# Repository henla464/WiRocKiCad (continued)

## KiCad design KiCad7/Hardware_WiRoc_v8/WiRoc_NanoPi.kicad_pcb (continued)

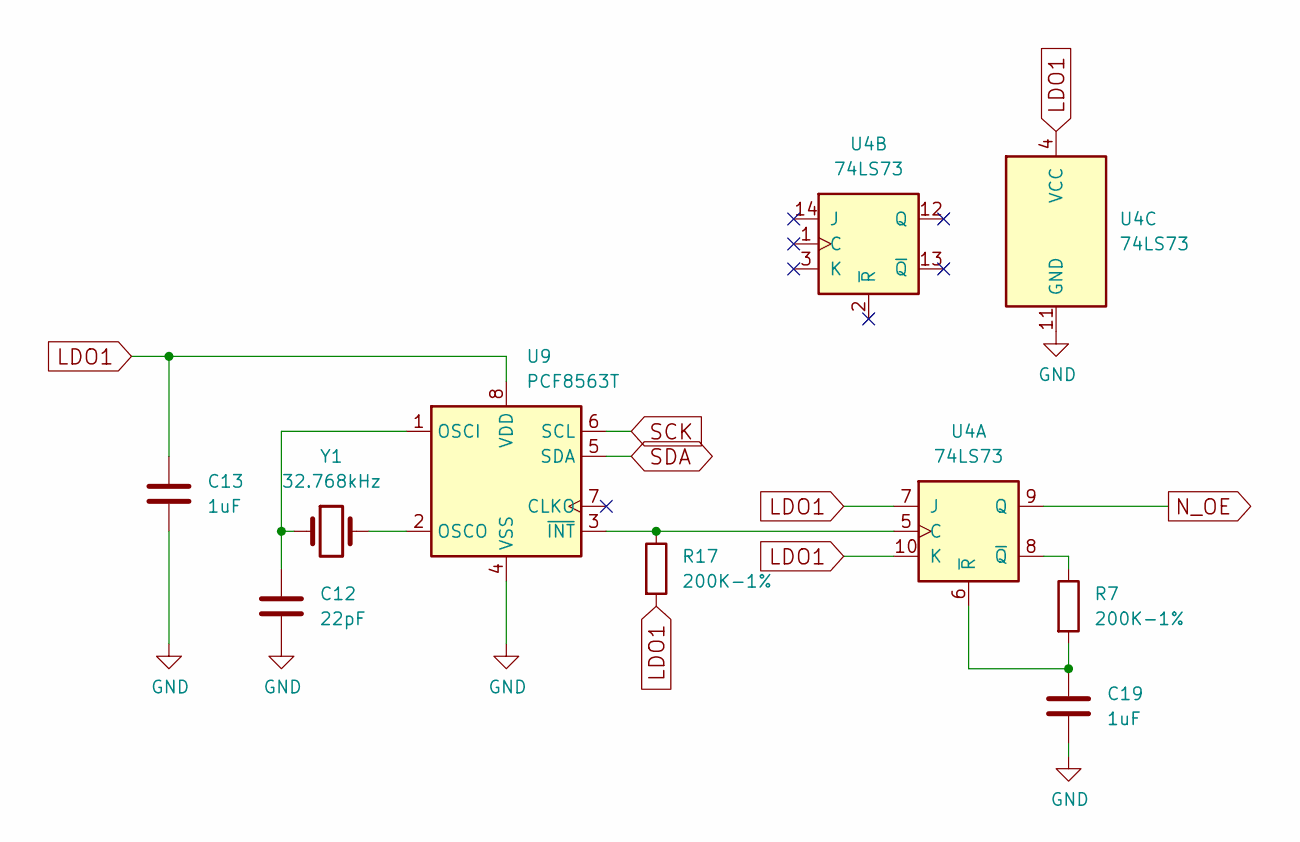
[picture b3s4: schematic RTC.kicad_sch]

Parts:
C12: 22pF; C_0402_1005Metric; ManufacturerPartNumber GRM155R71C223JA01D; LCSC Part # C1555
C13, C19: 1uF; C_0402_1005Metric; ManufacturerPartNumber CL10A105KB8NNNC; LCSC Part # C15849
R7, R17: 200K-1%; R_0402_1005Metric; ManufacturerPartNumber 0603WAF2003T5E; LCSC Part # C25811
U4: 74LS73; SOIC-14_3.9x8.7mm_P1.27mm; ManufacturerPartNumber CD74HC73M96; LCSC Part # C350539
U9: PCF8563T; SOIC-8_3.9x4.9mm_P1.27mm; ManufacturerPartNumber PCF8563T/5,518; LCSC Part # C7440
Y1: 32.768kHz; SMD3215-2P; ManufacturerPartNumber Q13FC1350000400; LCSC Part # C32346

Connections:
GND: C12.2, C13.2, C19.2, U4.11 (GND), U9.4 (VSS); also elsewhere on the board
LDO1: C13.1, R17.2, U4.4 (VCC), U4.7 (J), U4.10 (K), U9.8 (VDD); also elsewhere on the board
N_OE: U4.9 (Q); also elsewhere on the board
unnamed: R17.1, U4.5 (C), U9.3 (~INT)
unnamed: R7.1, U4.8 (~Q)
unnamed: C19.1, R7.2, U4.6 (~R)
unnamed: C12.1, U9.1 (OSCI), Y1.1
unnamed: U9.2 (OSCO), Y1.2
SCK: U9.6 (SCL); also elsewhere on the board
SDA: U9.5 (SDA); also elsewhere on the board

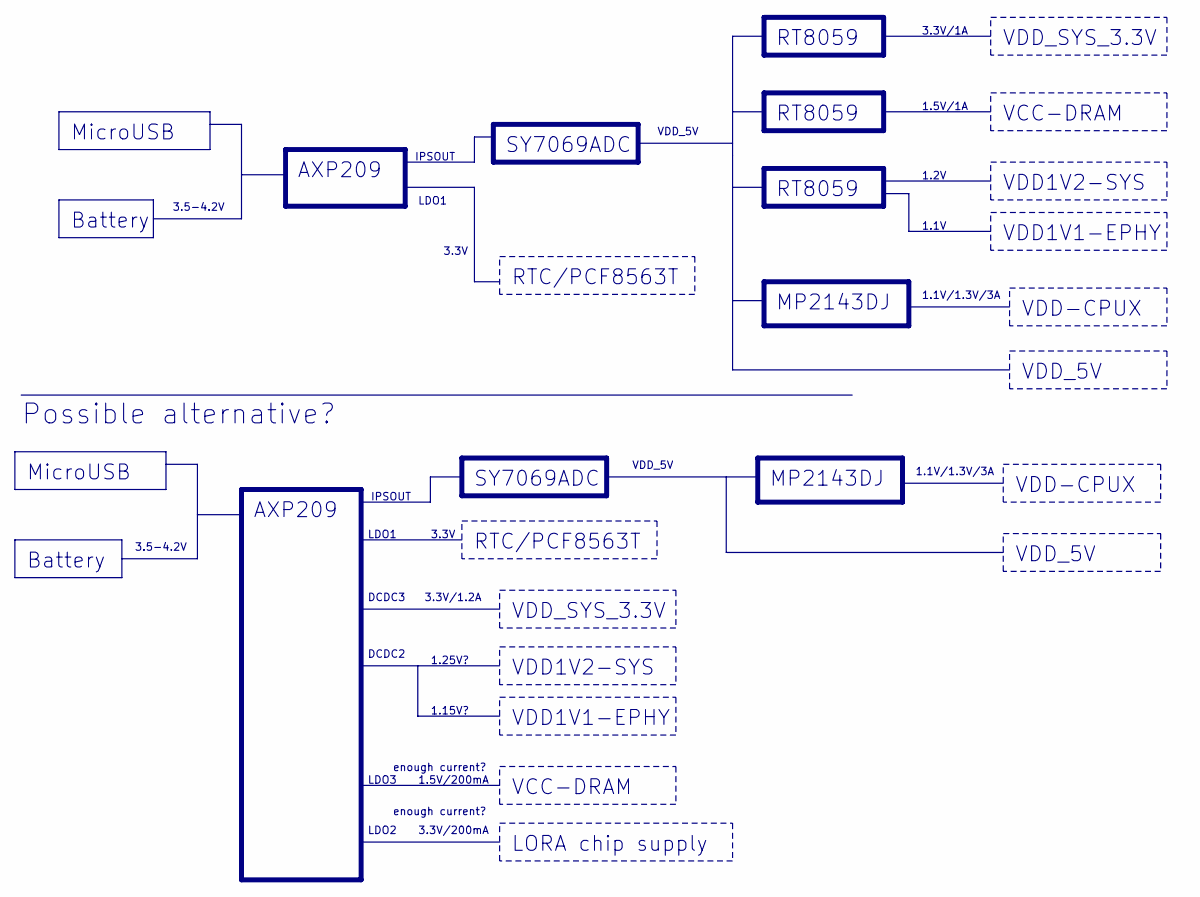
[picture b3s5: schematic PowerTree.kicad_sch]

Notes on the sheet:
VDD1V1-EPHY
VDD-CPUX
MicroUSB
RTC/PCF8563T
SY7069ADC
Battery
VDD1V2-SYS
MP2143DJ
RT8059
VDD_SYS_3.3V
VDD_5V
AXP209
VCC-DRAM
LORA chip supply
1.5V/1A
3.5-4.2V
DCDC3
1.1V/1.3V/3A
Possible alternative?
3.3V/1.2A
1.5V/200mA
1.25V?
IPSOUT
LDO2
3.3V/1A
3.3V/200mA
1.2V
1.15V?
DCDC2
LDO1
LDO3
3.3V
1.1V
enough current?

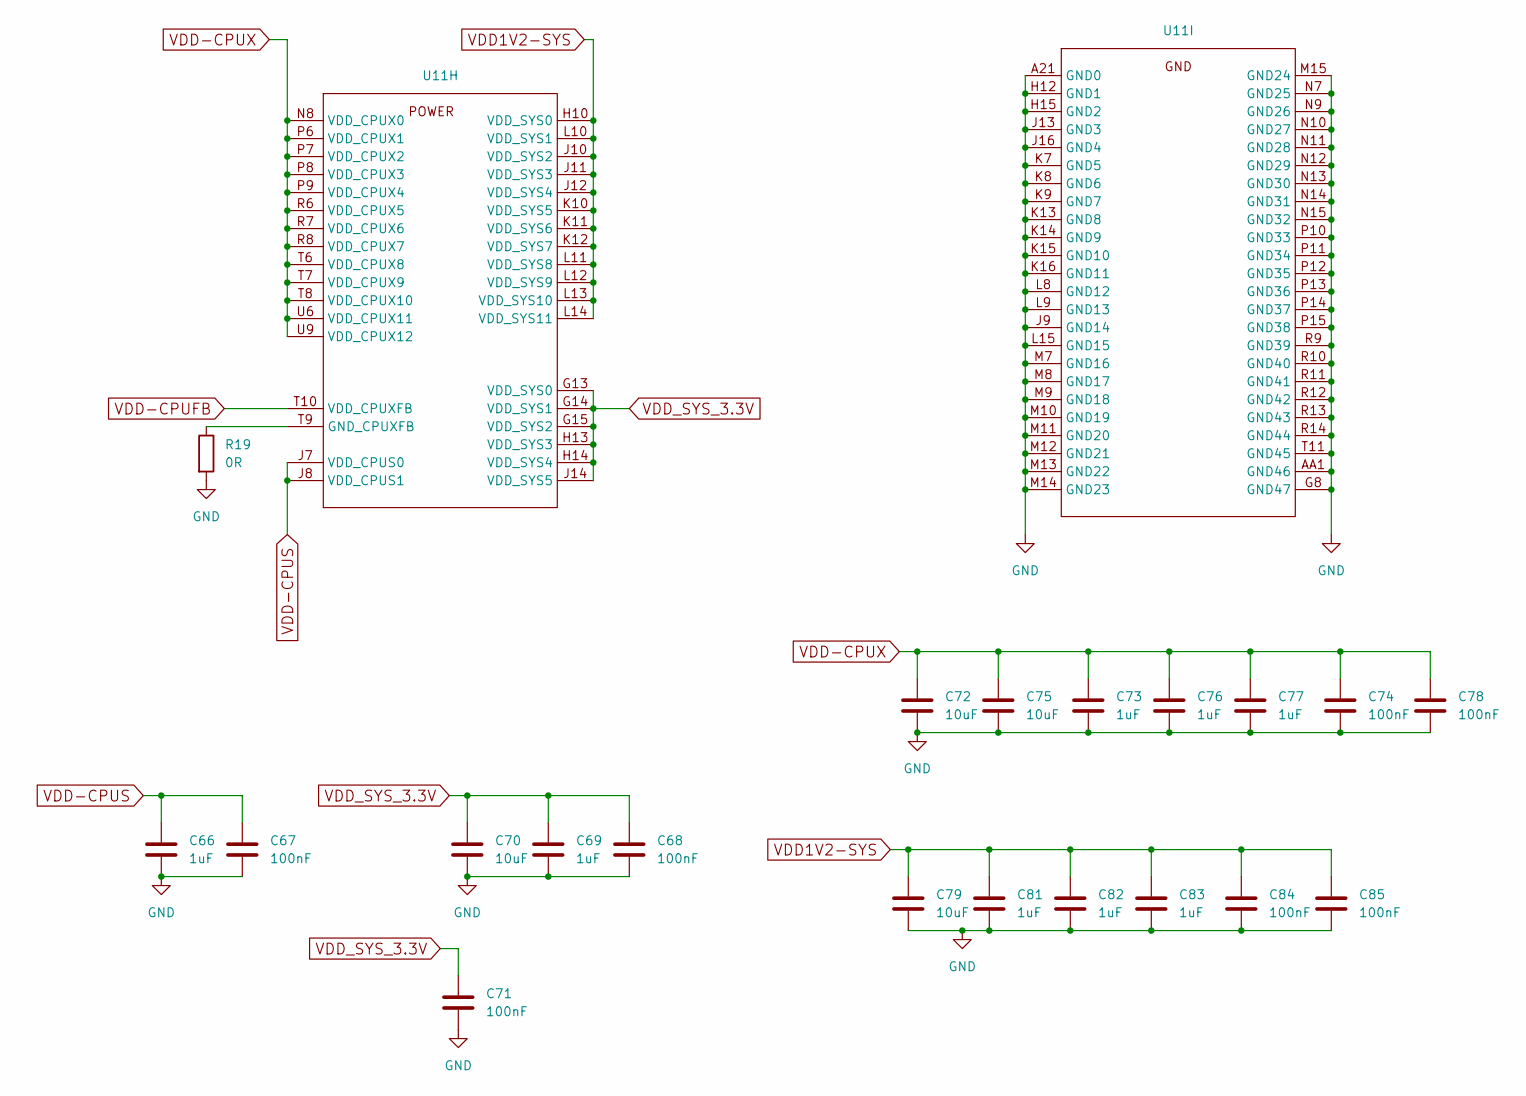
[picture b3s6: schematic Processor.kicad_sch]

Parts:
C66, C69, C73, C76, C77, C81, C82, C83: 1uF; C_0402_1005Metric
C67, C68, C71, C74, C78, C84, C85: 100nF; C_0402_1005Metric
C70, C72, C75, C79: 10uF; C_0402_1005Metric
R19: 0R; R_0402_1005Metric
U11: BGA-347_21x21_14.0x14.0mm

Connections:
GND: C66.2, C67.2, C68.2, C69.2, C70.2, C71.2, C72.2, C73.2, C74.2, C75.2, C76.2, C77.2, C78.2, C79.2, C81.2, C82.2, C83.2, C84.2, C85.2, R19.2, U11.A21 (GND0), U11.AA1 (GND46), U11.G8 (GND47), U11.H12 (GND1), U11.H15 (GND2), U11.J9 (GND14), U11.J13 (GND3), U11.J16 (GND4), U11.K7 (GND5), U11.K8 (GND6), U11.K9 (GND7), U11.K13 (GND8), U11.K14 (GND9), U11.K15 (GND10), U11.K16 (GND11), U11.L8 (GND12), U11.L9 (GND13), U11.L15 (GND15), U11.M7 (GND16), U11.M8 (GND17), U11.M9 (GND18), U11.M10 (GND19), U11.M11 (GND20), U11.M12 (GND21), U11.M13 (GND22), U11.M14 (GND23), U11.M15 (GND24), U11.N7 (GND25), U11.N9 (GND26), U11.N10 (GND27), U11.N11 (GND28), U11.N12 (GND29), U11.N13 (GND30), U11.N14 (GND31), U11.N15 (GND32), U11.P10 (GND33), U11.P11 (GND34), U11.P12 (GND35), U11.P13 (GND36), U11.P14 (GND37), U11.P15 (GND38), U11.R9 (GND39), U11.R10 (GND40), U11.R11 (GND41), U11.R12 (GND42), U11.R13 (GND43), U11.R14 (GND44), U11.T11 (GND45); also elsewhere on the board
unnamed: R19.1, U11.T9 (GND_CPUXFB)
VDD1V2-SYS: C79.1, C81.1, C82.1, C83.1, C84.1, C85.1, U11.H10 (VDD_SYS0), U11.J10 (VDD_SYS2), U11.J11 (VDD_SYS3), U11.J12 (VDD_SYS4), U11.K10 (VDD_SYS5), U11.K11 (VDD_SYS6), U11.K12 (VDD_SYS7), U11.L10 (VDD_SYS1), U11.L11 (VDD_SYS8), U11.L12 (VDD_SYS9), U11.L13 (VDD_SYS10), U11.L14 (VDD_SYS11); also elsewhere on the board
VDD-CPUFB: U11.T10 (VDD_CPUXFB); also elsewhere on the board
VDD-CPUS: C66.1, C67.1, U11.J7 (VDD_CPUS0), U11.J8 (VDD_CPUS1); also elsewhere on the board
VDD-CPUX: C72.1, C73.1, C74.1, C75.1, C76.1, C77.1, C78.1, U11.N8 (VDD_CPUX0), U11.P6 (VDD_CPUX1), U11.P7 (VDD_CPUX2), U11.P8 (VDD_CPUX3), U11.P9 (VDD_CPUX4), U11.R6 (VDD_CPUX5), U11.R7 (VDD_CPUX6), U11.R8 (VDD_CPUX7), U11.T6 (VDD_CPUX8), U11.T7 (VDD_CPUX9), U11.T8 (VDD_CPUX10), U11.U6 (VDD_CPUX11), U11.U9 (VDD_CPUX12); also elsewhere on the board
VDD_SYS_3.3V: C68.1, C69.1, C70.1, C71.1, U11.G13 (VDD_SYS0), U11.G14 (VDD_SYS1), U11.G15 (VDD_SYS2), U11.H13 (VDD_SYS3), U11.H14 (VDD_SYS4), U11.J14 (VDD_SYS5); also elsewhere on the board

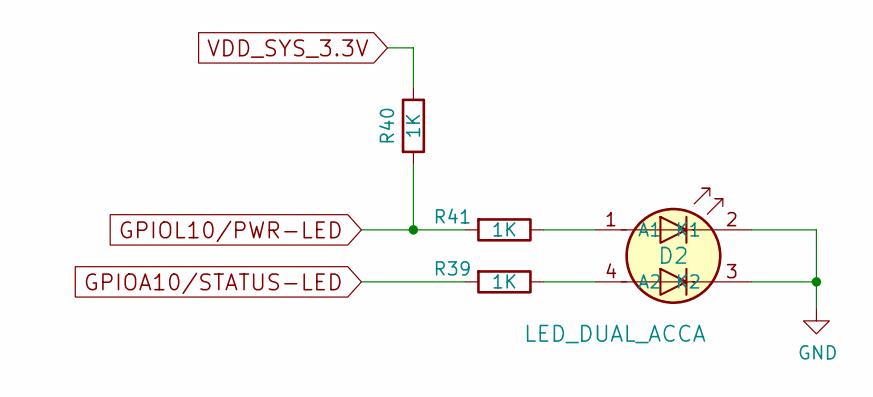
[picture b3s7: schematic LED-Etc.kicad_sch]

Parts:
D2: LED_DUAL_ACCA; LED_Dual_1.7_1.6; ManufacturerPartNumber HL-PCB-1617S9FH203BC; LCSC Part # C513363
R39, R40, R41: 1K; R_0402_1005Metric; ManufacturerPartNumber 0603WAJ0102T5E; LCSC Part # C21190

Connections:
GPIOA10/STATUS-LED: R39.2; also elsewhere on the board
GND: D2.2 (K1), D2.3 (K2); also elsewhere on the board
GPIOL10/PWR-LED: R40.2, R41.2; also elsewhere on the board
unnamed: D2.1 (A1), R41.1
unnamed: D2.4 (A2), R39.1
VDD_SYS_3.3V: R40.1; also elsewhere on the board

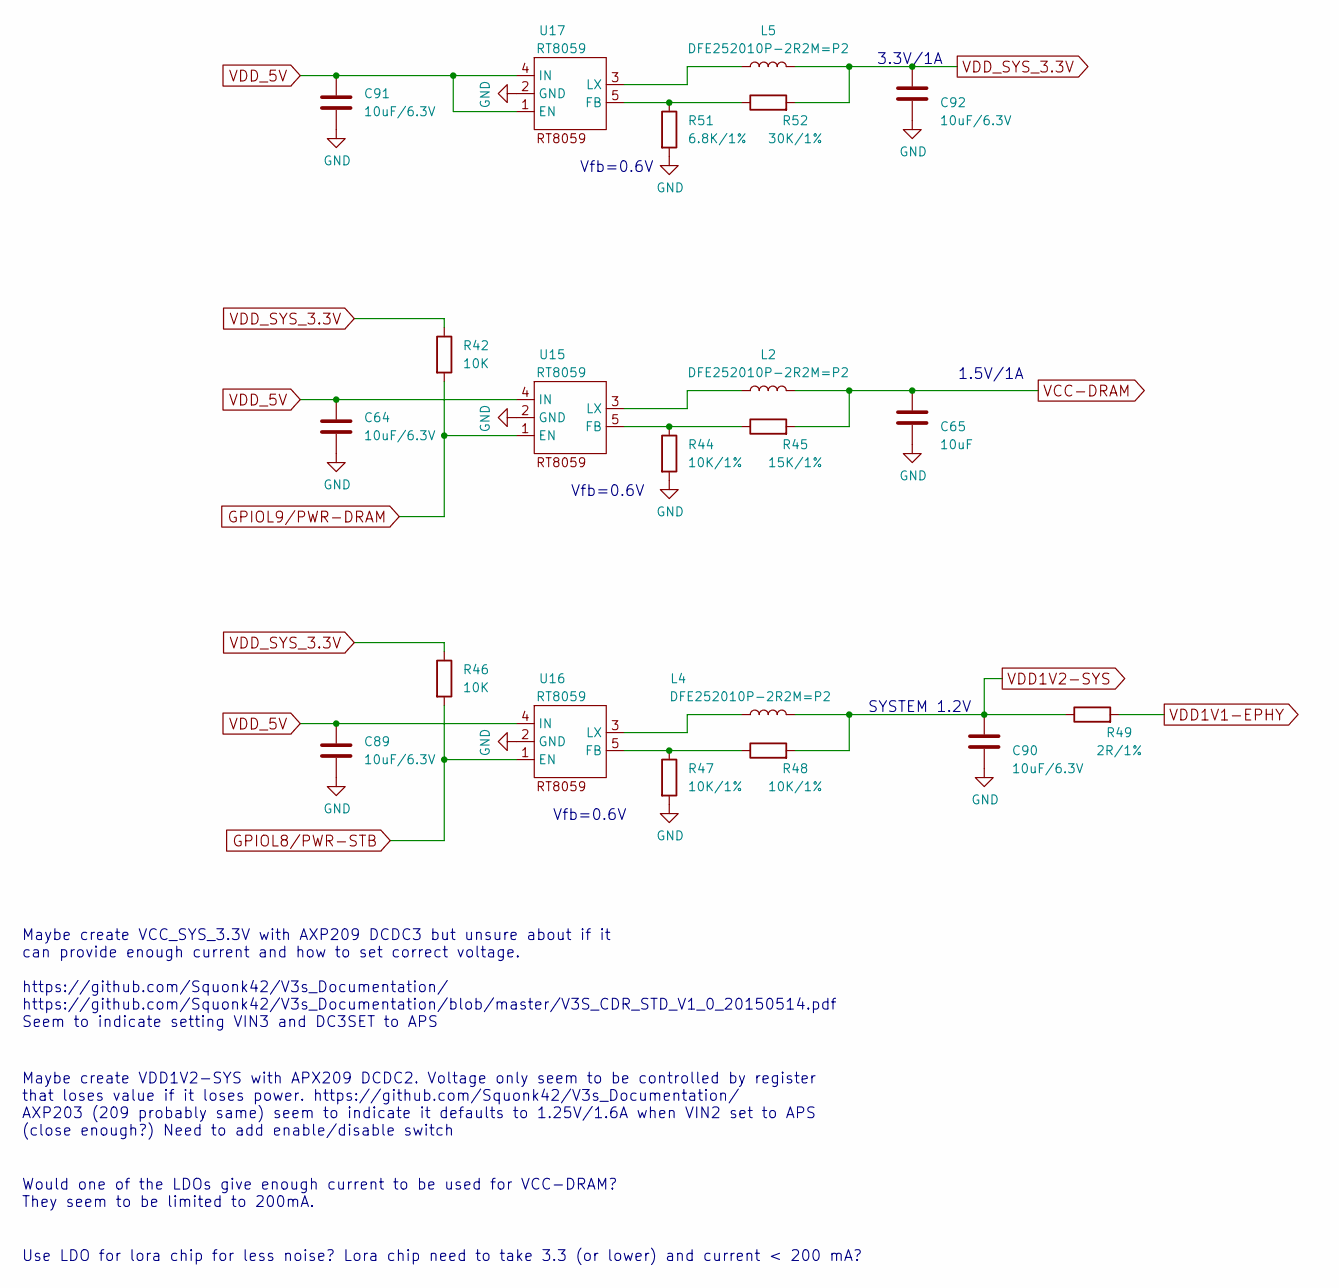
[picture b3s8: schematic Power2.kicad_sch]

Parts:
C64, C89, C90, C91, C92: 10uF/6.3V; C_0402_1005Metric
C65: 10uF; C_0402_1005Metric
L2, L4, L5: DFE252010P-2R2M=P2; L_1008_2520Metric
R42, R46: 10K; R_0402_1005Metric
R44, R47, R48: 10K/1%; R_0402_1005Metric
R45: 15K/1%; R_0402_1005Metric
R49: 2R/1%; R_0402_1005Metric
R51: 6.8K/1%; R_0402_1005Metric
R52: 30K/1%; R_0402_1005Metric
U15, U16, U17: RT8059; TSOT-23-5

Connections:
GND: C64.2, C65.2, C89.2, C90.2, C91.2, C92.2, R44.2, R47.2, R51.2, U15.2 (GND), U16.2 (GND), U17.2 (GND); also elsewhere on the board
GPIOL8/PWR-STB: R46.2, U16.1 (EN); also elsewhere on the board
GPIOL9/PWR-DRAM: R42.2, U15.1 (EN); also elsewhere on the board
unnamed: R44.1, R45.1, U15.5 (FB)
unnamed: L2.1, U15.3 (LX)
unnamed: R47.1, R48.1, U16.5 (FB)
unnamed: L4.1, U16.3 (LX)
unnamed: R51.1, R52.1, U17.5 (FB)
unnamed: L5.1, U17.3 (LX)
VCC-DRAM: C65.1, L2.2, R45.2; also elsewhere on the board
VDD1V1-EPHY: R49.2; also elsewhere on the board
VDD1V2-SYS: C90.1, L4.2, R48.2, R49.1; also elsewhere on the board
VDD_5V: C64.1, C89.1, C91.1, U15.4 (IN), U16.4 (IN), U17.1 (EN), U17.4 (IN); also elsewhere on the board
VDD_SYS_3.3V: C92.1, L5.2, R42.1, R46.1, R52.2; also elsewhere on the board

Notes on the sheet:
Vfb=0.6V
Maybe create VDD1V2-SYS with APX209 DCDC2. Voltage only seem to be controlled by register that loses value if it loses power. https://github.com/Squonk42/V3s_Documentation/ AXP203 (209 probably same) seem to indicate it defaults to 1.25V/1.6A when VIN2 set to APS (close enough?) Need to add enable/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
1.5V/1A
Maybe create VCC_SYS_3.3V with AXP209 DCDC3 but unsure about if it can provide enough current and how to set correct voltage. https://github.com/Squonk42/V3s_Documentation/ https://github.com/Squonk42/V3s_Documentation/blob/master/V3S_CDR_STD_V1_0_20150514.pdf Seem to indicate setting VIN3 and DC3S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
Would one of the LDOs give enough current to be used for VCC-DRAM? They seem to be limited to 200mA.
Use LDO for lora chip for less noise? Lora chip need to take 3.3 (or lower) and current < 200 mA?
3.3V/1A
SYSTEM 1.2V

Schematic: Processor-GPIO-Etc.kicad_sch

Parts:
C45: 100nF; C_0402_1005Metric
R25: 4,7K; R_0402_1005Metric
R33, R35: 10K; R_0402_1005Metric
R34: 22R; R_0402_1005Metric
U11: BGA-347_21x21_14.0x14.0mm

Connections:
GPIOA10/STATUS-LED: U11.E11 (PA10/SIM_DET/PA_EINT10); also elsewhere on the board
GND: C45.2, R33.2; also elsewhere on the board
IRQ: U11.E13 (PA3/UART2_CTS/JTAG_DI0/PA_EINT3); also elsewhere on the board
LORAAUX: U11.C3 (PG8/UART1_RTS/PG_EINT8); also elsewhere on the board
LORAEN: U11.D6 (PA2/UART2_RTS/JTAG_DO0/PA_EINT2); also elsewhere on the board
LORAMO: U11.C14 (PA17/SPDIF_OUT/PA_EINT17); also elsewhere on the board
unnamed: R33.1, U11.F16 (PC4/NAND_CE0)
unnamed: R34.1, U11.A17 (PC5/NAND_RE/SDC2_CLK)
unnamed: R35.1, U11.A16 (PC7/NAND_RB1)
unnamed: R25.2, U11.H6 (PA5/UART0_RX/PWM0/PA_EINT5)
SCK: U11.F11 (PA11/TWI0_SCK/DI_TX/PA_EINT11); also elsewhere on the board
SDA: U11.C13 (PA12/TWI0_SDA/DI_RX/PA_EINT12); also elsewhere on the board
SDC0-CLK: U11.D20 (PF2/SDC0_CLK/UART0_TX); also elsewhere on the board
SDC0-CMD: U11.F18 (PF3/SDC0_CMD/JTAG_DO0); also elsewhere on the board
SDC0-D0: U11.A19 (PF1/SDC0_D0/JTAG_DI0); also elsewhere on the board
SDC0-D1: U11.D19 (PF0/SDC0_D1/JTAG_MS0); also elsewhere on the board
SDC0-D2: U11.C20 (PF5/SDC0_D2/JTAG_CK0); also elsewhere on the board
SDC0-D3: U11.E21 (PF4/SDC0_D3/UART0_RX); also elsewhere on the board
SDC0-DET: U11.G18 (PF6); also elsewhere on the board
SRR_IRQ: U11.E14 (PA6/SIM_PWREN/PA_EINT6); also elsewhere on the board
SRR_NRST: U11.E3 (PG9/UART1_CTS/PG_EINT9); also elsewhere on the board
UART0_RX: R25.1; also elsewhere on the board
UART0_TX: U11.F5 (PA4/UART0_TX/PA_EINT4); also elsewhere on the board
UART1_RX: U11.D3 (PG7/UART1_RX/PG_EINT7); also elsewhere on the board
UART1_TX: U11.G4 (PG6/UART1_TX/PG_EINT6); also elsewhere on the board
UART2_RX: U11.D5 (PA1/UART2_RX/JTAG_CK0/PA_EINT1); also elsewhere on the board
UART2_TX: U11.D11 (PA0/UART2_TX/JTAG_MS0/PA_EINT0); also elsewhere on the board
VDD_SYS_3.3V: C45.1, R35.2, U11.H7 (VCC_PG), U11.J15 (VCC-PD); also elsewhere on the board
WIFI-DataReady: U11.L18 (PD16/MDC); also elsewhere on the board
WIFI-EN: U11.D2 (PG11/PCM1_CLK/PG_EINT11); also elsewhere on the board
WIFI-HandShake: U11.L19 (PD17/MDIO); also elsewhere on the board
WIFI-SPI-CS0: U11.B15 (PC3/NAND_CE1/SPI0_CS); also elsewhere on the board
WIFI-SPI-MISO: U11.C16 (PC1/NAND_ALE/SPI0_MISO); also elsewhere on the board
WIFI-SPI-MOSI: U11.C15 (PC0/NAND_WE/SPI0_MOSI); also elsewhere on the board
WIFI-SPI-SCLK: U11.B16 (PC2/NAND_CLE/SPI0_CLK); also elsewhere on the board
eMMC-CLK: R34.2; also elsewhere on the board
eMMC-CMD: U11.E16 (PC6/NAND_RB0/SDC2_CMD); also elsewhere on the board
eMMC-D0: U11.B18 (PC8/NAND_DQ0/SDC2_D0); also elsewhere on the board
eMMC-D1: U11.C17 (PC9/NAND_DQ1/SDC2_D1); also elsewhere on the board
eMMC-D2: U11.D17 (PC10/NAND_DQ2/SDC2_D2); also elsewhere on the board
eMMC-D3: U11.C18 (PC11/NAND_DQ3/SDC2_D3); also elsewhere on the board
eMMC-D4: U11.B17 (PC12/NAND_DQ4/SDC2_D4); also elsewhere on the board
eMMC-D5: U11.B19 (PC13/NAND_DQ5/SDC2_D5); also elsewhere on the board
eMMC-D6: U11.F17 (PC14/NAND_DQ6/SDC2_D6); also elsewhere on the board
eMMC-D7: U11.C19 (PC15/NAND_DQ7/SDC2_D7); also elsewhere on the board
eMMC-RST: U11.H16 (PC16/NAND_DQS/SDC2_RST); also elsewhere on the board

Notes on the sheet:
Bluetooth/wifi uart
WIFI
(GPIOG8=200, GPIOG9=201, GPIOG11=203)
USB OTG
PC1 was connected to N_VBUSEN but I don't think it was used.
GPIOG11 (was on gpio header)
LORAUX was previously on GPIOC0 SRR_NRST was previously on GPIOC3
(GPIOC0=64, GPIOC1=65, GPIOC2=66, GPIOC3=67)

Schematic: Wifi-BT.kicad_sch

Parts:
U19: ESP32-C6-Board; ESP32Hosted-C6-Board

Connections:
GND: U19.9 (GND); also elsewhere on the board
VDD_SYS_3.3V: U19.1 (VDD33); also elsewhere on the board
WIFI-DataReady: U19.3 (DataReady); also elsewhere on the board
WIFI-EN: U19.2 (EN); also elsewhere on the board
WIFI-HandShake: U19.4 (Handshake); also elsewhere on the board
WIFI-SPI-CS0: U19.8 (CS0); also elsewhere on the board
WIFI-SPI-MISO: U19.6 (MISO); also elsewhere on the board
WIFI-SPI-MOSI: U19.7 (MOSI); also elsewhere on the board
WIFI-SPI-SCLK: U19.5 (SCLK); also elsewhere on the board

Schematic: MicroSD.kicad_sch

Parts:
C30: 10uF/6.3V; C_0402_1005Metric
J3: Micro_SD_Card_Det1; TF-SMD_TF-018B-H15
R22: 33R; R_0402_1005Metric
R23, R24: 47K; R_0402_1005Metric
RV1, RV2, RV3, RV4, RV5, RV6, RV7, RV8: AVRL101A1R1NTB; R_0402_1005Metric

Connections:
GND: C30.1, J3.6 (VSS), J3.10 (SHIELD), RV1.2, RV2.2, RV3.2, RV4.2, RV5.2, RV6.2, RV7.2, RV8.2; also elsewhere on the board
unnamed: J3.5 (CLK), R22.2, RV6.1
SDC0-CLK: R22.1; also elsewhere on the board
SDC0-CMD: J3.3 (CMD), R23.1, RV1.1; also elsewhere on the board
SDC0-D0: J3.7 (DAT0), RV5.1; also elsewhere on the board
SDC0-D1: J3.8 (DAT1), RV4.1; also elsewhere on the board
SDC0-D2: J3.1 (DAT2), RV8.1; also elsewhere on the board
SDC0-D3: J3.2 (DAT3/CD), RV7.1; also elsewhere on the board
SDC0-DET: J3.9 (DET), R24.1, RV3.1; also elsewhere on the board
VDD_SYS_3.3V: C30.2, J3.4 (VDD), R23.2, R24.2, RV2.1; also elsewhere on the board

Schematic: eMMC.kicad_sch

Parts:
C32, C35, C80, C87, C88: 100nF; C_0402_1005Metric
C33, C34, C86: 1uF; C_0402_1005Metric
R26: 10K; R_0402_1005Metric
U14: KLM8G1WEPD-B031; MICRON_EMMC_153

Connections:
GND: C32.2, C33.2, C34.2, C35.2, C80.2, C86.2, C87.2, C88.2, U14.A6 (Vss), U14.C4 (Vss), U14.D4 (NC33), U14.E7 (Vss), U14.G5 (Vss), U14.H10 (Vss), U14.J5 (Vss), U14.K8 (Vss), U14.N2 (Vss), U14.N5 (Vss), U14.P2 (NC102), U14.P4 (Vss), U14.P6 (Vss), U14.P8 (NC103); also elsewhere on the board
unnamed: C32.1, C33.1, U14.C1 (NC19), U14.C2 (VDDI)
VDD_SYS_3.3V: C34.1, C35.1, C80.1, C86.1, C87.1, C88.1, R26.1, U14.C6 (VDD), U14.E6 (VDDF), U14.F5 (VDDF), U14.J10 (VDDF), U14.K9 (VDDF), U14.M4 (VDD), U14.N4 (VDD), U14.P3 (VDD), U14.P5 (VDD); also elsewhere on the board
eMMC-CLK: U14.M6 (CLK); also elsewhere on the board
eMMC-CMD: R26.2, U14.M5 (CMD); also elsewhere on the board
eMMC-D0: U14.A3 (DAT0); also elsewhere on the board
eMMC-D1: U14.A4 (DAT1); also elsewhere on the board
eMMC-D2: U14.A5 (DAT2); also elsewhere on the board
eMMC-D3: U14.B1 (NC10), U14.B2 (DAT3); also elsewhere on the board
eMMC-D4: U14.A2 (NC2), U14.B3 (DAT4); also elsewhere on the board
eMMC-D5: U14.B4 (DAT5), U14.C3 (NC20), U14.D1 (NC30), U14.D2 (NC31); also elsewhere on the board
eMMC-D6: U14.B5 (DAT6), U14.C5 (NC21); also elsewhere on the board
eMMC-D7: U14.A7 (RFU1), U14.B6 (DAT7); also elsewhere on the board
eMMC-RST: U14.K5 (RSTN); also elsewhere on the board

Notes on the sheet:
* Connected to simplify fanout from the eMMC chip

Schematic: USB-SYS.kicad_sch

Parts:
C31, C37, C39, C42, C43: 100nF; C_0402_1005Metric
C36: 1uF; C_0402_1005Metric
C38, C44: 4.7uF; C_0402_1005Metric
C40, C41: 18pF; C_0402_1005Metric
R27: 47K; R_0402_1005Metric
R28: 100K; R_0402_1005Metric
R29, R30, R31, R32: 10K; R_0402_1005Metric
R43: 0R; R_0402_1005Metric
U11: BGA-347_21x21_14.0x14.0mm
U13: SGM803-RXN3L; SOT-23-3
Y2: 24MHz/18pF; Crystal_SMD_2520-4Pin_2.5x2.0mm

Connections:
AP-RESET: C42.1, R29.2, U11.V6 (RESET), U13.2 (/RESET)
GND: C31.2, C36.1, C37.2, C38.2, C39.1, C40.1, C41.1, C42.2, C43.2, C44.2, U11.H8 (GND_TV), U11.M5 (HGND), U11.U3 (AGND), U13.1 (GND), Y2.2, Y2.4; also elsewhere on the board
GPIOL6/CPUX-VSET: U11.T4 (PL6/S_JTAG_DO/S_PL_EINT6); also elsewhere on the board
GPIOL8/PWR-STB: U11.T2 (PL8/S_PL_EINT8); also elsewhere on the board
GPIOL9/PWR-DRAM: U11.M6 (PL9/S_PL_EINT9); also elsewhere on the board
GPIOL10/PWR-LED: U11.V2 (PL10/S_PWM/S_PL_EINT10); also elsewhere on the board
LORARS: U11.U2 (PL11/S_CIR_RX/S_PL_EINT11); also elsewhere on the board
unnamed: R30.1, U11.R1 (PL3/S_UART_RX/S_PL_EINT3)
unnamed: R31.1, U11.N2 (PL4/S_JTAG_MS/S_PL_EINT4)
unnamed: C36.2, U11.W3 (MBIAS)
unnamed: R28.2, U11.AA5 (KEYADC)
unnamed: R27.2, U11.AA6 (NMI)
unnamed: R32.1, U11.W6 (UBOOT)
unnamed: C39.2, R43.1, U11.N3 (VCC_PLL)
unnamed: C38.1, U11.H11 (VDD_EFUSEBP)
USBHost-DM1: U11.A8 (USB_DM2); also elsewhere on the board
USBHost-DM2: U11.B9 (USB_DM3); also elsewhere on the board
USBHost-DP1: U11.A7 (USB_DP2); also elsewhere on the board
USBHost-DP2: U11.B8 (USB_DP3); also elsewhere on the board
VDD1V1-EPHY: U11.F8 (EPHY_VDD); also elsewhere on the board
VDD-CPUS: C44.1, U11.M4 (RTC_VIO); also elsewhere on the board
VDD_SYS_3.3V: C31.1, C37.1, C43.1, R27.1, R28.1, R29.1, R30.2, R31.2, R32.2, R43.2, U11.G7 (EPHY_VCC), U11.G9 (V33_TV), U11.G10 (VDD_EFUSE), U11.G11 (VCC-USB), U11.J6 (HVCC), U11.K6 (VCC_RTC), U11.V3 (AVCC), U13.3 (Vin); also elsewhere on the board
X24MI: C40.2, U11.K2 (X24MIN), Y2.1
X24MO: C41.2, U11.K1 (X24MOUT), Y2.3

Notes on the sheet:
ZeroPi uses a ferrite bead
Close to IC
Note: ZeroPi used 22pF capacitor and crystal has value "XTAL-2520-4P"
wifi clock,shouldn't be needed
WIFI (enable)

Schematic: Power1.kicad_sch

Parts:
C93, C95, C96: 10uF/6.3V; C_0402_1005Metric
C94: 22pF; C_0402_1005Metric
L6: DFE252010P-1R0M=P2; L_1008_2520Metric
Q1: L2N7002WT1G; SOT-323_SC-70
R50: 10K/1%; R_0402_1005Metric
R53: 12K/1%; R_0402_1005Metric
R54: 30K/1%; R_0402_1005Metric
R55: 10K; R_0402_1005Metric
U18: MP2143DJ; TSOT-23-8-Thinner-Pads

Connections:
GND: C93.2, C95.2, C96.2, Q1.2 (S), R53.1, U18.4 (GND), U18.6 (GND1); also elsewhere on the board
GPIOL6/CPUX-VSET: Q1.1 (G), R55.1; also elsewhere on the board
GPIOL8/PWR-STB: U18.8 (EN); also elsewhere on the board
unnamed: Q1.3 (D), R54.1
unnamed: C94.2, R50.1, R53.2, R54.2, U18.7 (FB)
unnamed: L6.1, U18.3 (SW)
VDD-CPUFB: C94.1, R50.2; also elsewhere on the board
VDD-CPUX: C95.1, C96.1, L6.2, U18.5 (OUT); also elsewhere on the board
VDD_5V: C93.1, U18.2 (VIN); also elsewhere on the board
VDD_SYS_3.3V: R55.2; also elsewhere on the board

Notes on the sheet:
GPIOL6/CPUX-VSET = 0, VDD-CPUX=1.1V GPIOL6/CPUX-VSET = 1, VDD-CPUX=1.3V
1.1V/1.3V/3A
Vfb=0.6V

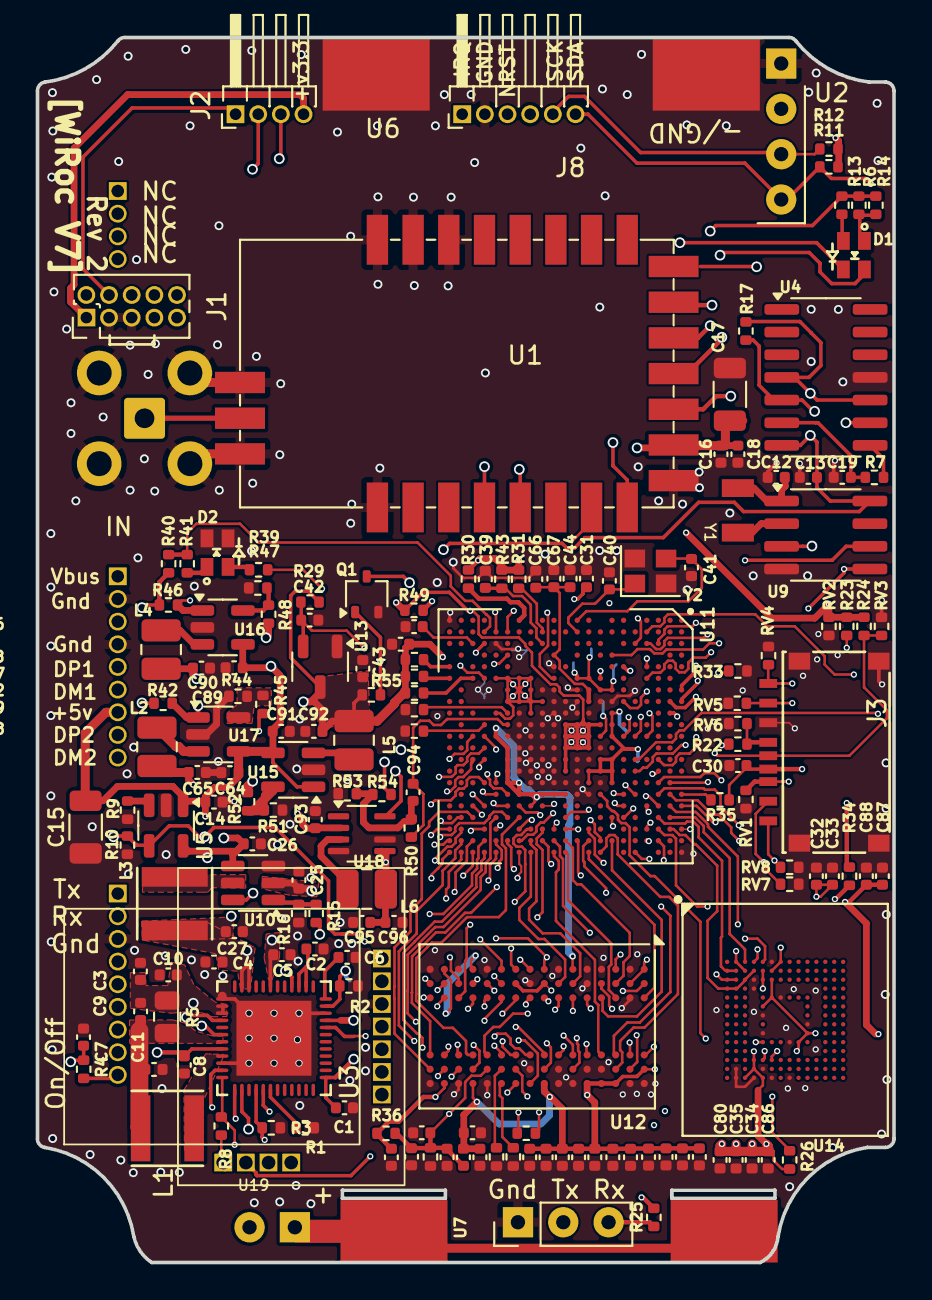
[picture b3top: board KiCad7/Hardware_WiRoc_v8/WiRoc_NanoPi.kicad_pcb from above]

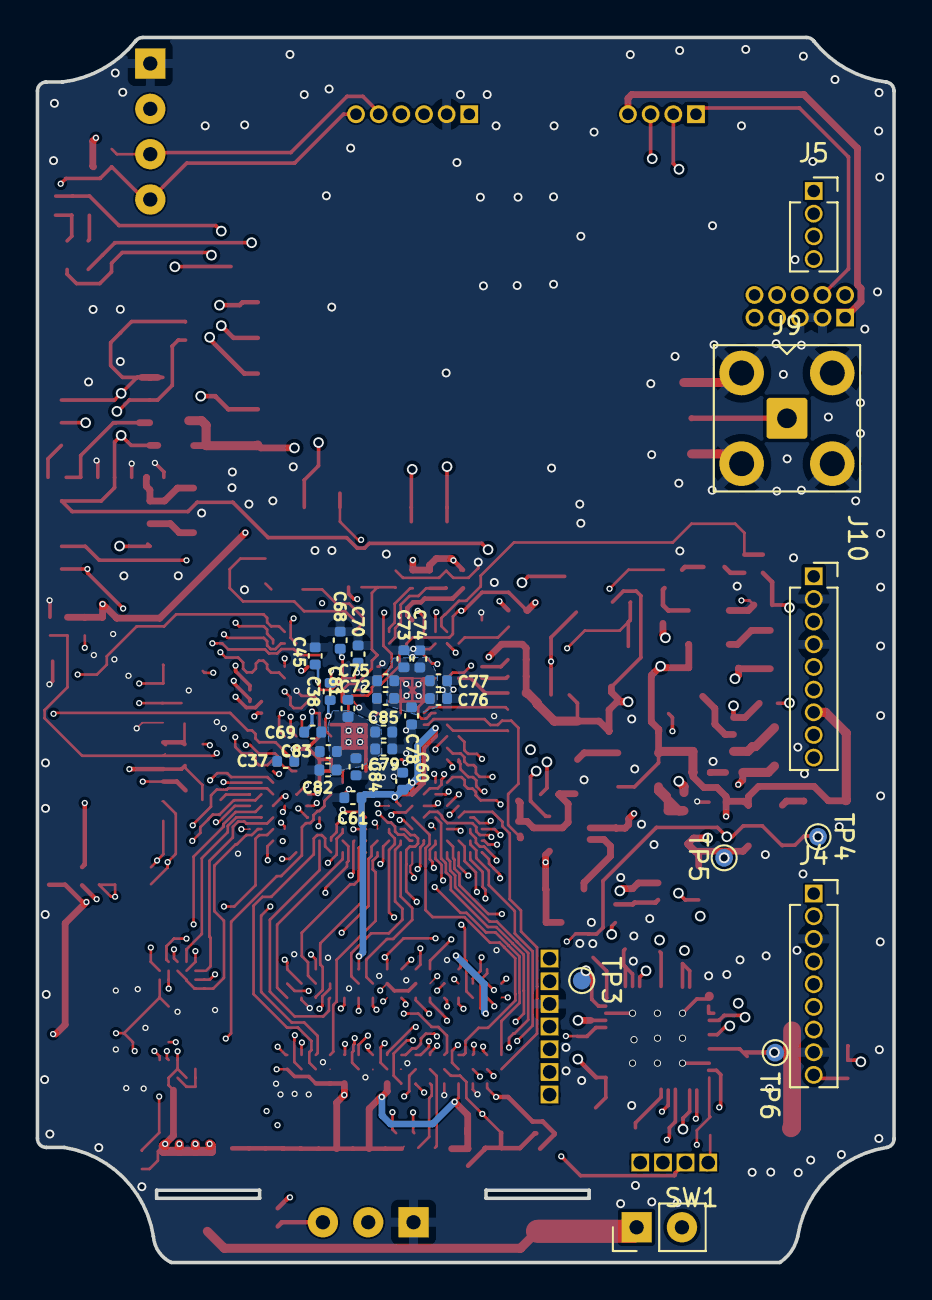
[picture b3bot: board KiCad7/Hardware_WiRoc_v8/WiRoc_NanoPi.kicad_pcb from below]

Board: 6 copper layers, 48.0 x 68.7 mm, 197 parts (30 on the bottom side), 178 nets.

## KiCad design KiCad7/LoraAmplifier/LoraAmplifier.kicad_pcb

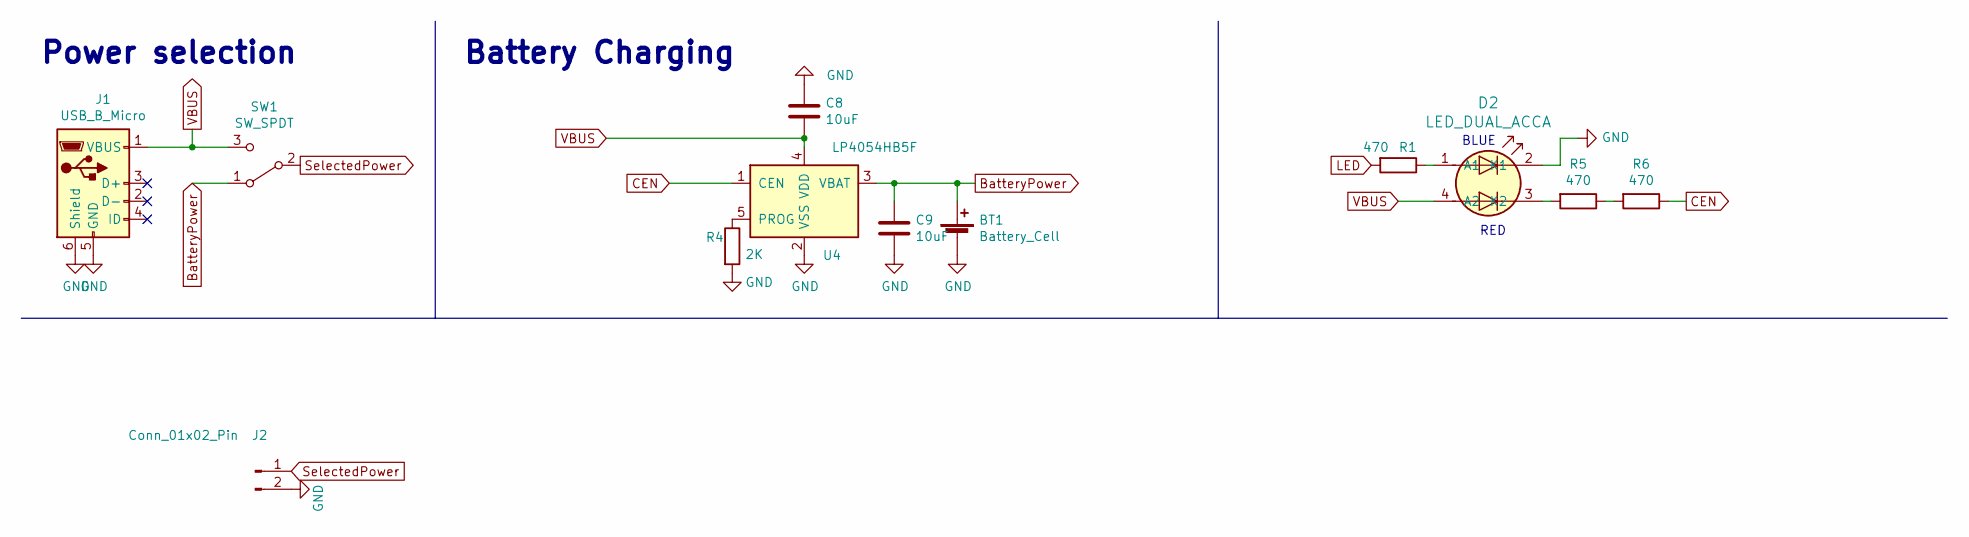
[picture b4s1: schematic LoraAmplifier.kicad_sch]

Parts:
BT1: Battery_Cell; JST_2.56
C8, C9: 10uF; C_0805_2012Metric_Pad1.15x1.40mm_HandSolder; ManufacturerPartNumber CL21A106KOQNNNE; LCSCPartNumber C1713
D2: LED_DUAL_ACCA; LED_Dual_1.7_1.6; ManufacturerPartNumber HL-PCB-1617S9FH203BC; LCSCPartNumber C513363
J1: USB_B_Micro; USB_Micro-B_Horizontal; ManufacturerPartNumber U254-051T-4BH83-F1S; LCSCPartNumber C397452
J2: Conn_01x02_Pin; JST_2.56
R1, R5, R6: 470; R_0805_2012Metric_Pad1.15x1.40mm_HandSolder; ManufacturerPartNumber 0805W8F4700T5E; LCSCPartNumber C17710
R4: 2K; R_0805_2012Metric_Pad1.15x1.40mm_HandSolder; ManufacturerPartNumber 0805W8F2001T5E; LCSCPartNumber C17604
SW1: SW_SPDT; SW_SPDT_PCM12; ManufacturerPartNumber SK-3296S-01-L3; LCSCPartNumber C319019
U4: LP4054HB5F; SOT-23-5; ManufacturerPartNumber LP4054HB5F; LCSCPartNumber C517187

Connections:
BatteryPower: BT1.1 (+), C9.1, SW1.1 (A), U4.3 (VBAT)
CEN: R6.1, U4.1 (CEN)
GND: BT1.2 (-), C8.1, C9.2, D2.2 (K1), J1.5 (GND), J1.6 (Shield), J2.2, R4.2, U4.2 (VSS)
unnamed: D2.1 (A1), R1.1
unnamed: D2.3 (K2), R5.2
unnamed: R5.1, R6.2
unnamed: R4.1, U4.5 (PROG)
SelectedPower: J2.1, SW1.2 (B)
VBUS: C8.2, D2.4 (A2), J1.1 (VBUS), SW1.3 (C), U4.4 (VDD)

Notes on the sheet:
Battery Charging
RED
BLUE
Power selection

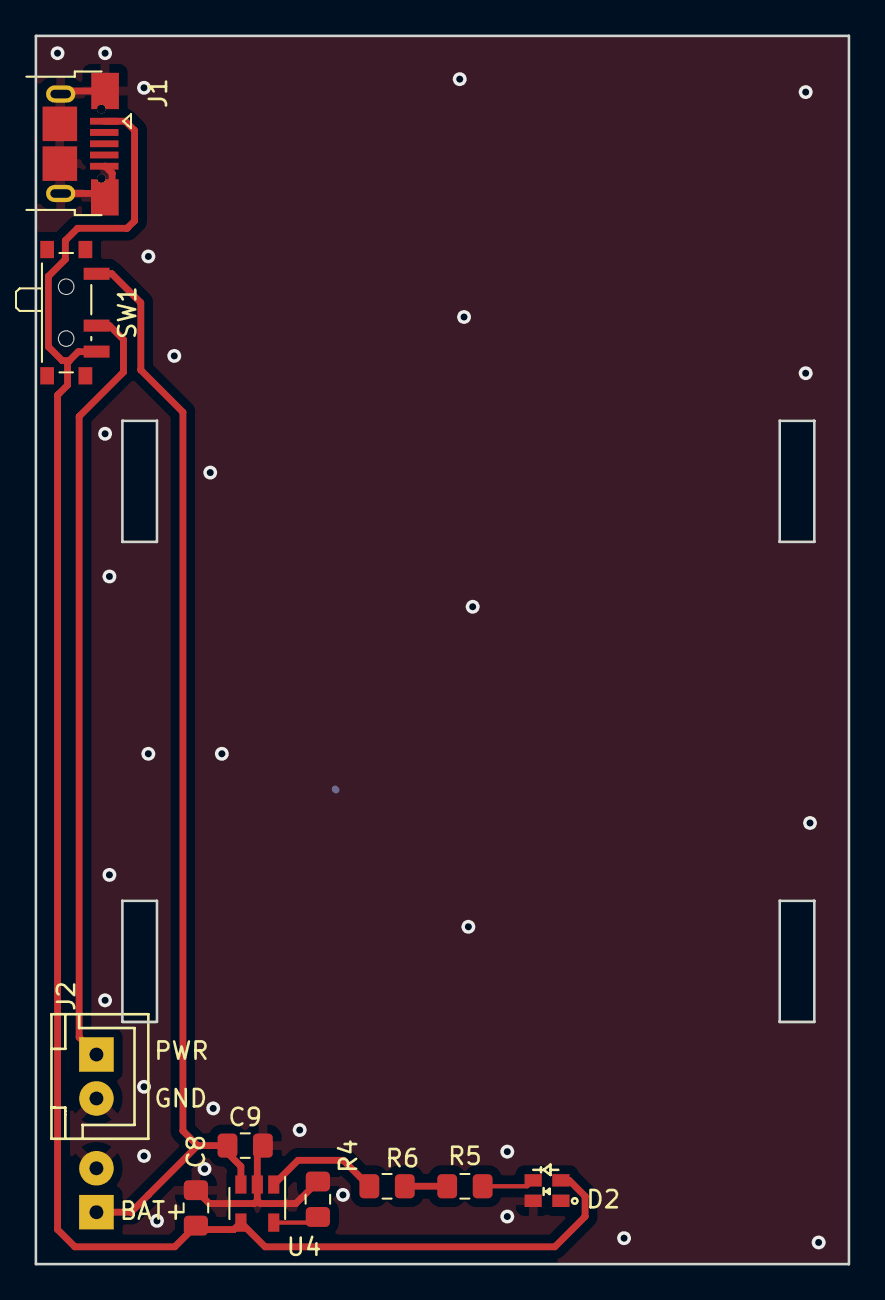
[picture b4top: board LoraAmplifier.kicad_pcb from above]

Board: 2 copper layers, 47.0 x 71.0 mm, 11 parts (1 on the bottom side), 8 nets.

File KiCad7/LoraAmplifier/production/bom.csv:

Designator,Footprint,Quantity,Value,LCSC Part #
BT1,JST_2.56,1,Battery_Cell,
"C8, C9",0805,2,10uF,
D2,LED_Dual_1.7_1.6,1,LED_DUAL_ACCA,
J1,USB_Micro-B_Horizontal,1,USB_B_Micro,
J2,JST_2.56,1,Conn_01x02_Pin,
R4,0805,1,2K,
"R5, R6",0805,2,470,
SW1,SW_SPDT_PCM12,1,SW_SPDT,
U4,SOT-23-5,1,LP4054HB5F,

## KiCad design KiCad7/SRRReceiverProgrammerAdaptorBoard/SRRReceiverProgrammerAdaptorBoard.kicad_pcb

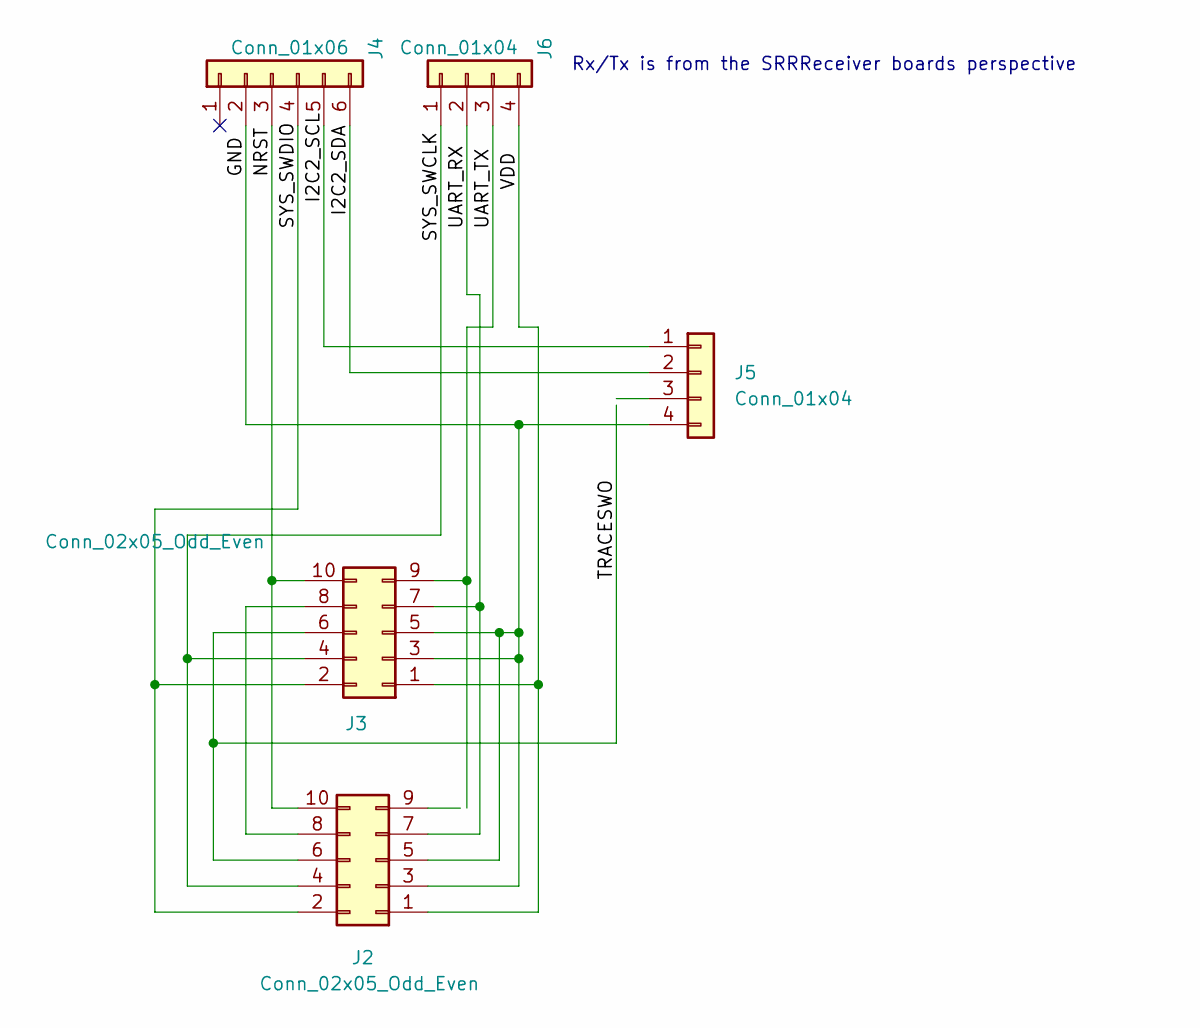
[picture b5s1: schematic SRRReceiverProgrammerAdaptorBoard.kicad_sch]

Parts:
J2, J3: Conn_02x05_Odd_Even; PinHeader_2x05_P1.27mm_Vertical
J4: Conn_01x06; PinHeader_1x06_P1.27mm_Horizontal
J5: Conn_01x04; PinHeader_1x04_P2.54mm_Vertical
J6: Conn_01x04; PinHeader_1x04_P1.27mm_Horizontal

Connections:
/GND: J2.3, J2.5, J3.3, J3.5, J4.2, J5.4
/I2C2_SCL: J4.5, J5.1
/I2C2_SDA: J4.6, J5.2
/NRST: J2.10, J3.10, J4.3
/SYS_SWCLK: J2.4, J3.4, J6.1
/SYS_SWDIO: J2.2, J3.2, J4.4
/TRACESWO: J2.6, J3.6
/UART_RX: J2.7, J3.7, J6.2
/UART_TX: J3.9, J6.3
/VDD: J2.1, J3.1, J6.4
unnamed: J2.8, J3.8

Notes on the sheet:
Rx/Tx is from the SRRReceiver boards perspective
